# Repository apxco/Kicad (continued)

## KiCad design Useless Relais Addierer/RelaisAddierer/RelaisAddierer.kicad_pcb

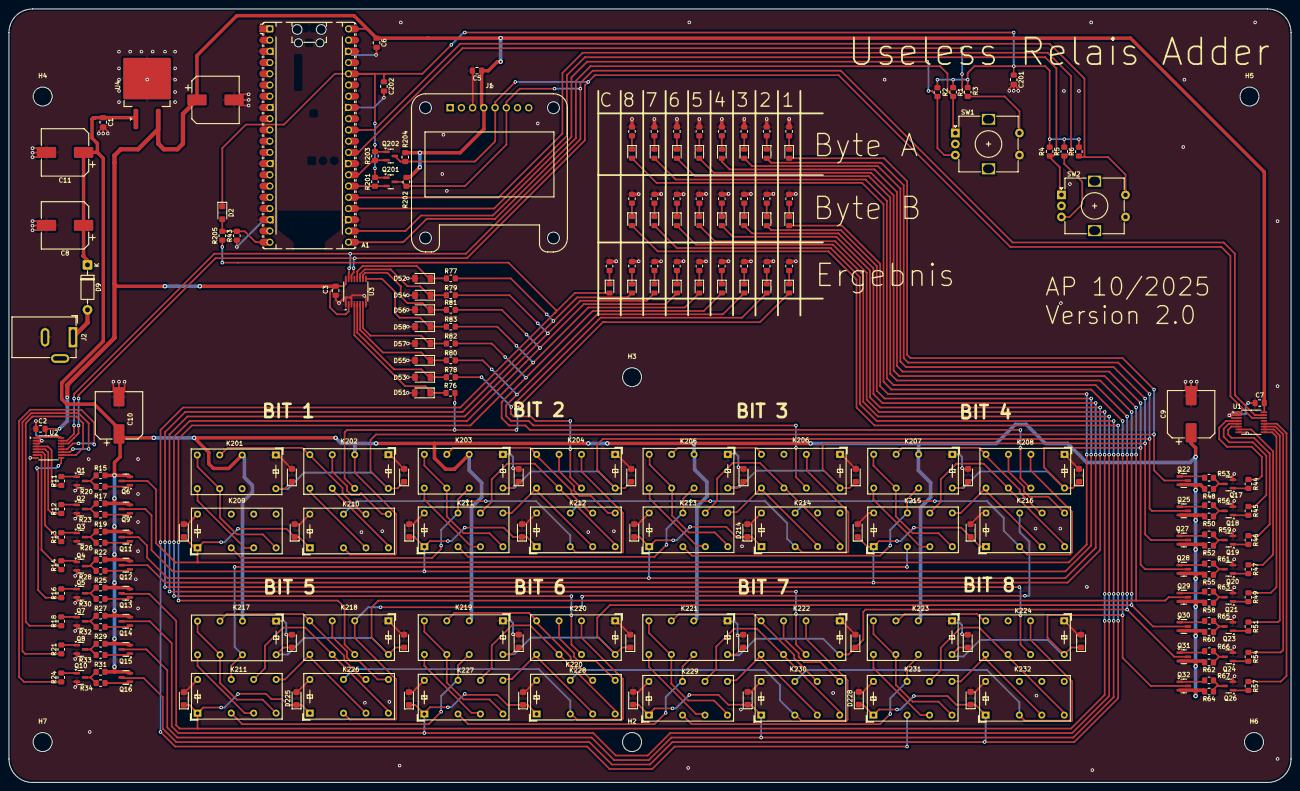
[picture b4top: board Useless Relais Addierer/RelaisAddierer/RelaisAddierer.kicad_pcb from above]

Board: 2 copper layers, 290.1 x 175.0 mm, 254 parts (0 on the bottom side), 198 nets.

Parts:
A1: RaspberryPi_Pico; RaspberryPi_Pico_Common_Unspecified
C1: 1uF; C_0805_2012Metric_Pad1.18x1.45mm_HandSolder
C2, C3, C5, C6, C7, C201, C202: 100nF; C_0805_2012Metric_Pad1.18x1.45mm_HandSolder
C8, C9, C10, C11, C12: 470uF; CP_Elec_10x12.5
D2, D201, D202, D203, D204, D205, D206, D207, D208, D209, D210, D211, D212, D213, D214, D215, D216, D217, D218, D219, D220, D221, D222, D223, D224, D225, D226, D227, D228, D229, D230, D231, D232: 1N4148WT; D_SMF
D9: 1N4007; D_DO-41_SOD81_P10.16mm_Horizontal
D34, D35, D36, D37, D38, D39, D40, D41, D43, D44, D45, D46, D47, D48, D49, D50, D59, D60, D61, D62, D63, D64, D65, D66, D67: LED; LED_0805_2012Metric_Pad1.15x1.40mm_HandSolder
D51, D52, D53, D54, D55, D56, D57, D58: BZD27C47; D_MiniMELF
H2, H3, H4, H5, H6, H7: MountingHole; MountingHole_4.3mm_M4_DIN965
J1: Conn_01x08_Pin; Adafruit_SSD1306
J2: Barrel_Jack; BarrelJack_GCT_DCJ200-10-A_Horizontal
K201, K202, K203, K204, K205, K206, K207, K208, K209, K210, K211, K212, K213, K214, K215, K216, K217, K218, K219, K220, K221, K222, K223, K224, K225, K226, K227, K228, K229, K230, K231, K232: HK19F-DCxxV-SHC; Relay_DPDT_Finder_30.22
Q1, Q2, Q3, Q4, Q5, Q7, Q8, Q10, Q17, Q18, Q19, Q20, Q21, Q23, Q24, Q26: BC847; SOT-23
Q6: PJM10H01PSA; SOT-23
Q9, Q11, Q12, Q13, Q14, Q15, Q16, Q22, Q25, Q27, Q28, Q29, Q30, Q31, Q32: DMP3099L; SOT-23
Q201, Q202: BSS138; SOT-23
R1, R2, R3, R4, R5, R6, R15, R17, R19, R22, R25, R27, R29, R31, R48, R50, R52, R55, R58, R60, R62, R64, R201, R202, R203, R204: 10k; R_0805_2012Metric_Pad1.20x1.40mm_HandSolder
R11, R12, R13, R14, R16, R18, R20, R21, R23, R24, R26, R28, R30, R32, R33, R34, R44, R45, R46, R47, R49, R51, R53, R54, R56, R57, R59, R61, R63, R65, R66, R67: 100R; R_0805_2012Metric_Pad1.20x1.40mm_HandSolder
R35, R36, R37, R38, R39, R40, R41, R42, R43, R68, R69, R70, R71, R72, R73, R74, R75, R84, R85, R86, R87, R88, R89, R90, R91, R92: 1k; R_0805_2012Metric_Pad1.20x1.40mm_HandSolder
R76, R77, R78, R79, R80, R81, R82, R83: 560; R_0805_2012Metric_Pad1.20x1.40mm_HandSolder
R205: 2,6k; R_0805_2012Metric_Pad1.20x1.40mm_HandSolder
SW1, SW2: RotaryEncoder_Switch; RotaryEncoder_Alps_EC12E-Switch_Vertical_H20mm
U1, U2, U3: TCA9534; TSSOP-16_4.4x5mm_P0.65mm
U4: uA7805; TO-263-2

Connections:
+3.3V: A1.36 (3V3), C201.1, C202.1, D2.1 (K), Q201.1 (G), Q202.1 (G), R1.1, R2.2, R3.2, R4.1, R5.2, R6.2, R201.2, R203.2
+5V: A1.40 (VBUS), C2.1, C3.1, C5.1, C6.1, C7.1, C12.1, J1.4, R202.2, R204.2, U1.16 (VDD), U2.1 (A0), U2.16 (VDD), U3.2 (A1), U3.16 (VDD), U4.3 (OUT)
+12V: C1.1, C8.1, C9.1, C10.1, C11.1, D9.1 (K), K201.11, K202.11, K203.11, K205.11, K207.11, K210.11, K217.11, K219.11, K221.11, K223.11, Q6.2 (S), Q9.2 (S), Q11.2 (S), Q12.2 (S), Q13.2 (S), Q14.2 (S), Q15.2 (S), Q16.2 (S), Q22.2 (S), Q25.2 (S), Q27.2 (S), Q28.2 (S), Q29.2 (S), Q30.2 (S), Q31.2 (S), Q32.2 (S), R15.2, R17.2, R19.2, R22.2, R25.2, R27.2, R29.2, R31.2, R48.2, R50.2, R52.2, R55.2, R58.2, R60.2, R62.2, R64.2, U4.1 (IN)
Bit A.1: D43.2 (A), D201.1 (K), D204.1 (K), K201.A2, K202.A2, Q22.3 (D)
Bit A.2: D44.2 (A), D205.1 (K), D208.1 (K), K203.A2, K204.A2, Q25.3 (D)
Bit A.3: D45.2 (A), D202.1 (K), D206.1 (K), K205.A2, K206.A2, Q27.3 (D)
Bit A.4: D46.2 (A), D203.1 (K), D207.1 (K), K207.A2, K208.A2, Q28.3 (D)
Bit A.5: D47.2 (A), D217.1 (K), D221.1 (K), K217.A2, K218.A2, Q29.3 (D)
Bit A.6: D48.2 (A), D220.1 (K), D224.1 (K), K219.A2, K220.A2, Q30.3 (D)
Bit A.7: D49.2 (A), D218.1 (K), D222.1 (K), K221.A2, K222.A2, Q31.3 (D)
Bit A.8: D50.2 (A), D219.1 (K), D223.1 (K), K223.A2, K224.A2, Q32.3 (D)
Bit B.1: D34.2 (A), D209.1 (K), D210.1 (K), K209.A1, K210.A1, Q6.3 (D)
Bit B.2: D35.2 (A), D213.1 (K), D216.1 (K), K211.A1, K212.A1, Q9.3 (D)
Bit B.3: D36.2 (A), D211.1 (K), D214.1 (K), K213.A1, K214.A1, Q11.3 (D)
Bit B.4: D37.2 (A), D212.1 (K), D215.1 (K), K215.A1, K216.A1, Q12.3 (D)
Bit B.5: D38.2 (A), D225.1 (K), D226.1 (K), K225.A1, K226.A1, Q13.3 (D)
Bit B.6: D39.2 (A), D229.1 (K), D232.1 (K), K227.A1, K228.A1, Q14.3 (D)
Bit B.7: D40.2 (A), D227.1 (K), D230.1 (K), K229.A1, K230.A1, Q15.3 (D)
Bit B.8: D41.2 (A), D228.1 (K), D231.1 (K), K231.A1, K232.A1, Q16.3 (D)
CLK1: A1.21 (GPIO16), R1.2, SW1.A
CLK2: A1.24 (GPIO18), R4.2, SW2.A
Carry_Bit1: K203.21, K209.11, K211.21
Carry_Bit1_neg: K204.11, K210.21, K212.11
Carry_Bit2: K205.21, K211.11, K213.21
Carry_Bit2_neg: K206.11, K212.21, K214.11
Carry_Bit3: K207.21, K213.11, K215.21
Carry_Bit3_neg: K208.11, K214.21, K216.11
Carry_Bit4: K215.11, K217.21, K225.21
Carry_Bit4_neg: K216.21, K218.11, K226.11
Carry_Bit5: K219.21, K225.11, K227.21
Carry_Bit5_neg: K220.11, K226.21, K228.11
Carry_Bit6: K221.21, K227.11, K229.21
Carry_Bit6_neg: K222.11, K228.21, K230.11
Carry_Bit7: K223.21, K229.11, K231.21
Carry_Bit7_neg: K224.11, K230.21, K232.11
Carry_Bit8: D59.2 (A), K231.11, R205.1
DT1: A1.22 (GPIO17), R2.1, SW1.B
DT2: A1.25 (GPIO19), R5.1, SW2.B
GND: A1.3 (GND), A1.8 (GND), A1.13 (GND), A1.18 (GND), A1.23 (GND), A1.28 (GND), A1.33 (AGND), A1.38 (GND), C1.2, C2.2, C3.2, C5.2, C6.2, C7.2, C8.2, C9.2, C10.2, C11.2, C12.2, C201.2, C202.2, D51.2 (A), D52.2 (A), D53.2 (A), D54.2 (A), D55.2 (A), D56.2 (A), D57.2 (A), D58.2 (A), D201.2 (A), D202.2 (A), D203.2 (A), D204.2 (A), D205.2 (A), D206.2 (A), D207.2 (A), D208.2 (A), D209.2 (A), D210.2 (A), D211.2 (A), D212.2 (A), D213.2 (A), D214.2 (A), D215.2 (A), D216.2 (A), D217.2 (A), D218.2 (A), D219.2 (A), D220.2 (A), D221.2 (A), D222.2 (A), D223.2 (A), D224.2 (A), D225.2 (A), D226.2 (A), D227.2 (A), D228.2 (A), D229.2 (A), D230.2 (A), D231.2 (A), D232.2 (A), J1.3, J2.2, K201.A1, K202.A1, K203.A1, K204.A1, K205.A1, K206.A1, K207.A1, K208.A1, K209.A2, K210.A2, K211.A2, K212.A2, K213.A2, K214.A2, K215.A2, K216.A2, K217.A1, K218.A1, K219.A1, K220.A1, K221.A1, K222.A1, K223.A1, K224.A1, K225.A2, K226.A2, K227.A2, K228.A2, K229.A2, K230.A2, K231.A2, K232.A2, Q1.2 (E), Q2.2 (E), Q3.2 (E), Q4.2 (E), Q5.2 (E), Q7.2 (E), Q8.2 (E), Q10.2 (E), Q17.2 (E), Q18.2 (E), Q19.2 (E), Q20.2 (E), Q21.2 (E), Q23.2 (E), Q24.2 (E), Q26.2 (E), R35.2, R36.2, R37.2, R38.2, R39.2, R40.2, R41.2, R42.2, R43.1, R68.2, R69.2, R70.2, R71.2, R72.2, R73.2, R74.2, R75.2, R84.2, R85.2, R86.2, R87.2, R88.2, R89.2, R90.2, R91.2, R92.2, SW1.C, SW1.S2, SW2.C, SW2.S2, U1.1 (A0), U1.2 (A1), U1.3 (A2), U1.8 (GND), U2.2 (A1), U2.3 (A2), U2.8 (GND), U3.1 (A0), U3.3 (A2), U3.8 (GND), U4.2 (GND)
I2C0 SCL: J1.5, Q202.3 (D), R204.1, U1.14 (SCL), U2.14 (SCL), U3.14 (SCL)
I2C0 SDA: J1.6, Q201.3 (D), R202.1, U1.15 (SDA), U2.15 (SDA), U3.15 (SDA)
unnamed: A1.20 (GPIO15), D2.2 (A), R43.2, R205.2
unnamed: A1.26 (GPIO20), Q201.2 (S), R201.1
unnamed: A1.27 (GPIO21), Q202.2 (S), R203.1
unnamed: D9.2 (A), J2.1
unnamed: D34.1 (K), R35.1
unnamed: D35.1 (K), R36.1
unnamed: D36.1 (K), R37.1
unnamed: D37.1 (K), R38.1
unnamed: D38.1 (K), R39.1
unnamed: D39.1 (K), R40.1
unnamed: D40.1 (K), R41.1
unnamed: D41.1 (K), R42.1
unnamed: D43.1 (K), R68.1
unnamed: D44.1 (K), R69.1
unnamed: D45.1 (K), R70.1
unnamed: D46.1 (K), R71.1
unnamed: D47.1 (K), R72.1
unnamed: D48.1 (K), R73.1
unnamed: D49.1 (K), R74.1
unnamed: D50.1 (K), R75.1
unnamed: D51.1 (K), R76.1, U3.4 (P0)
unnamed: D52.1 (K), R77.1, U3.12 (P7)
unnamed: D53.1 (K), R78.1, U3.5 (P1)
unnamed: D54.1 (K), R79.1, U3.11 (P6)
unnamed: D55.1 (K), R80.1, U3.6 (P2)
unnamed: D56.1 (K), R81.1, U3.10 (P5)
unnamed: D57.1 (K), R82.1, U3.7 (P3)
unnamed: D58.1 (K), R83.1, U3.9 (P4)
unnamed: D59.1 (K), R84.1
unnamed: D60.1 (K), R85.1
unnamed: D61.1 (K), R86.1
unnamed: D62.1 (K), R87.1
unnamed: D63.1 (K), R88.1
unnamed: D64.1 (K), R89.1
unnamed: D65.1 (K), R90.1
unnamed: D66.1 (K), R91.1
unnamed: D67.1 (K), R92.1
unnamed: K201.12, K202.14, K210.22
unnamed: K201.14, K201.22, K209.14
unnamed: K201.24, K209.12
unnamed: K202.12, K210.24
unnamed: K202.22, K210.14
unnamed: K202.24, K210.12
unnamed: K203.12, K204.14, K212.22
unnamed: K203.14, K203.22, K211.14
unnamed: K203.24, K211.12
unnamed: K204.12, K212.24
unnamed: K204.22, K211.22, K212.14
unnamed: K204.24, K211.24, K212.12
unnamed: K205.12, K206.14
unnamed: K205.14, K205.22, K213.14
unnamed: K205.24, K213.12
unnamed: K206.22, K213.22, K214.14
unnamed: K206.24, K213.24, K214.12
unnamed: K207.12, K208.14, K216.22
unnamed: K207.14, K207.22, K215.14
unnamed: K207.24, K215.12
unnamed: K208.12, K216.24
unnamed: K208.22, K215.22, K216.14
unnamed: K208.24, K215.24, K216.12
unnamed: K217.12, K218.14, K226.22
unnamed: K217.14, K217.22, K225.14
unnamed: K217.24, K225.12
unnamed: K218.12, K226.24
unnamed: K218.22, K225.22, K226.14
unnamed: K218.24, K225.24, K226.12
unnamed: K219.12, K220.14, K228.22
unnamed: K219.14, K219.22, K227.14
unnamed: K219.24, K227.12
unnamed: K220.12, K228.24
unnamed: K220.22, K227.22, K228.14
unnamed: K220.24, K227.24, K228.12
unnamed: K221.12, K222.14, K230.22
unnamed: K221.14, K221.22, K229.14
unnamed: K221.24, K229.12
unnamed: K222.12, K230.24
unnamed: K222.22, K229.22, K230.14
unnamed: K222.24, K229.24, K230.12
unnamed: K223.12, K224.14
unnamed: K223.14, K223.22, K231.14
unnamed: K223.24, K231.12
unnamed: K224.22, K231.22, K232.14
unnamed: K224.24, K231.24, K232.12
unnamed: Q1.1 (B), R11.2
unnamed: Q1.3 (C), R15.1, R20.1
unnamed: Q2.1 (B), R12.2
unnamed: Q2.3 (C), R17.1, R23.1
unnamed: Q3.1 (B), R13.2
unnamed: Q3.3 (C), R19.1, R26.1
unnamed: Q4.1 (B), R14.2
unnamed: Q4.3 (C), R22.1, R28.1
unnamed: Q5.1 (B), R16.2
unnamed: Q5.3 (C), R25.1, R30.1
unnamed: Q6.1 (G), R20.2
unnamed: Q7.1 (B), R18.2
unnamed: Q7.3 (C), R27.1, R32.1
unnamed: Q8.1 (B), R21.2
unnamed: Q8.3 (C), R29.1, R33.1
unnamed: Q9.1 (G), R23.2
unnamed: Q10.1 (B), R24.2
unnamed: Q10.3 (C), R31.1, R34.1
unnamed: Q11.1 (G), R26.2
unnamed: Q12.1 (G), R28.2
unnamed: Q13.1 (G), R30.2
unnamed: Q14.1 (G), R32.2
unnamed: Q15.1 (G), R33.2
unnamed: Q16.1 (G), R34.2
unnamed: Q17.1 (B), R44.2
unnamed: Q17.3 (C), R48.1, R53.1
unnamed: Q18.1 (B), R45.2
unnamed: Q18.3 (C), R50.1, R56.1
unnamed: Q19.1 (B), R46.2
unnamed: Q19.3 (C), R52.1, R59.1
unnamed: Q20.1 (B), R47.2
unnamed: Q20.3 (C), R55.1, R61.1
unnamed: Q21.1 (B), R49.2
unnamed: Q21.3 (C), R58.1, R63.1
unnamed: Q22.1 (G), R53.2
unnamed: Q23.1 (B), R51.2
unnamed: Q23.3 (C), R60.1, R65.1
unnamed: Q24.1 (B), R54.2
unnamed: Q24.3 (C), R62.1, R66.1
unnamed: Q25.1 (G), R56.2
unnamed: Q26.1 (B), R57.2
unnamed: Q26.3 (C), R64.1, R67.1
unnamed: Q27.1 (G), R59.2
unnamed: Q28.1 (G), R61.2
unnamed: Q29.1 (G), R63.2
unnamed: Q30.1 (G), R65.2
unnamed: Q31.1 (G), R66.2
unnamed: Q32.1 (G), R67.2
unnamed: R44.1, U1.4 (P0)
unnamed: R45.1, U1.5 (P1)
unnamed: R46.1, U1.6 (P2)
unnamed: R47.1, U1.7 (P3)
unnamed: R49.1, U1.9 (P4)
unnamed: R51.1, U1.10 (P5)
unnamed: R54.1, U1.11 (P6)
unnamed: R57.1, U1.12 (P7)
unnamed: R11.1, U2.4 (P0)
unnamed: R12.1, U2.5 (P1)
unnamed: R13.1, U2.6 (P2)
unnamed: R14.1, U2.7 (P3)
unnamed: R16.1, U2.9 (P4)
unnamed: R18.1, U2.10 (P5)
unnamed: R21.1, U2.11 (P6)
unnamed: R24.1, U2.12 (P7)
SW1: A1.29 (GPIO22), R3.1, SW1.S1
SW2: A1.31 (GPIO26_ADC0), R6.1, SW2.S1
Summ_Bit1: D67.2 (A), K202.21, R76.2
Summ_Bit2: D66.2 (A), K204.21, R78.2
Summ_Bit3: D65.2 (A), K206.21, R80.2
Summ_Bit4: D64.2 (A), K208.21, R82.2
Summ_Bit5: D63.2 (A), K218.21, R83.2
Summ_Bit6: D62.2 (A), K220.21, R81.2
Summ_Bit7: D61.2 (A), K222.21, R79.2
Summ_Bit8: D60.2 (A), K224.21, R77.2

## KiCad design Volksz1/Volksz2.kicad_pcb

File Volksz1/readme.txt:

Hat für RaspberryPi, Spannungsversorung und Interface für Volkszähler.

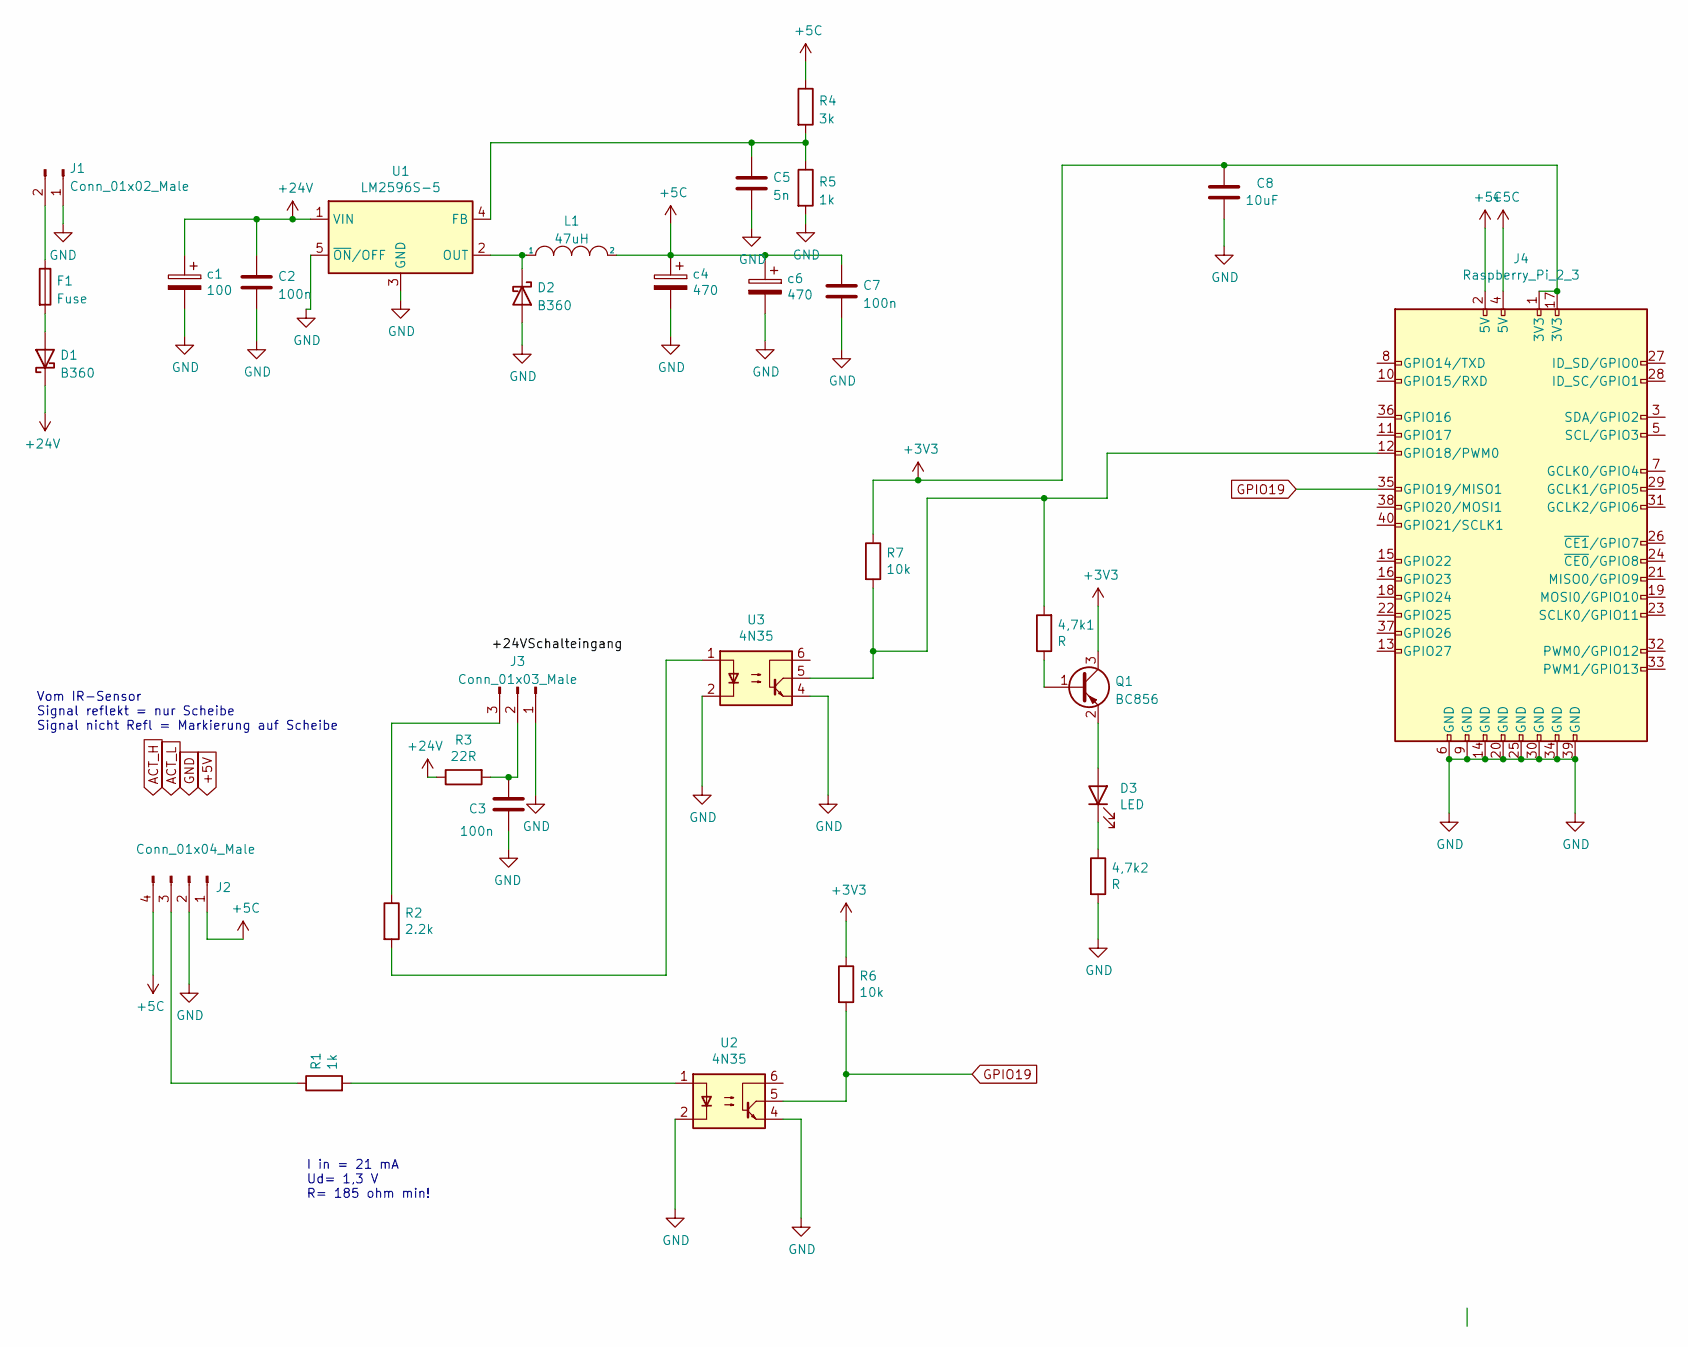
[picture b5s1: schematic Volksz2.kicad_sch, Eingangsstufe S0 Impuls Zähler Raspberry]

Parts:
4,7k1, 4,7k2: R; R_0805_2012Metric_Pad1.20x1.40mm_HandSolder
C2, C3, C7: 100n; C_0805_2012Metric_Pad1.18x1.45mm_HandSolder
C5: 5n; C_0805_2012Metric_Pad1.18x1.45mm_HandSolder
C8: 10uF; R_0805_2012Metric_Pad1.20x1.40mm_HandSolder
D1, D2: B360; D_SMC
D3: LED; D_0805_2012Metric_Pad1.15x1.40mm_HandSolder
F1: Fuse; Fuse_0805_2012Metric_Pad1.15x1.40mm_HandSolder
J1: Conn_01x02_Male; PinSocket_1x02_P2.54mm_Vertical
J2: Conn_01x04_Male; PinHeader_1x04_P2.54mm_Vertical
J3: Conn_01x03_Male; PinHeader_1x03_P2.54mm_Vertical
J4: Raspberry_Pi_2_3; PinSocket_2x20_P2.54mm_Vertical
L1: 47uH; L_Wuerth_HCI-1040
Q1: BC856; SOT-23
R1, R5: 1k; R_0805_2012Metric_Pad1.20x1.40mm_HandSolder
R2: 2.2k; R_0805_2012Metric_Pad1.20x1.40mm_HandSolder
R3: 22R; R_1206_3216Metric_Pad1.30x1.75mm_HandSolder
R4: 3k; R_0805_2012Metric_Pad1.20x1.40mm_HandSolder
R6, R7: 10k; R_0805_2012Metric_Pad1.20x1.40mm_HandSolder
U1: LM2596S-5; TO-263-5_TabPin3
U2, U3: 4N35; DIP-6_W7.62mm
c1: 100; CP_Elec_10x12.6
c4, c6: 470; CP_Elec_10x12.6

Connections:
+3V3: C8.1, J4.1 (3V3), J4.17 (3V3), Q1.3 (C), R6.1, R7.1
+5C: C7.1, J2.1, J2.4, J4.2 (5V), J4.4 (5V), L1.2, R4.1, c4.1, c6.1
+24V: C2.1, D1.1 (K), R3.1, U1.1 (VIN), c1.1
GND: 4,7k2.2, C2.2, C3.2, C5.2, C7.2, C8.2, D2.2 (A), J1.1, J2.2, J3.1, J4.6 (GND), J4.9 (GND), J4.14 (GND), J4.20 (GND), J4.25 (GND), J4.30 (GND), J4.34 (GND), J4.39 (GND), R5.2, U1.3 (GND), U1.5 (~ON/OFF), U2.2, U2.4, U3.2, U3.4, c1.2, c4.2, c6.2
GPIO19: J4.35 (GPIO19/MISO1), R6.2, U2.5
unnamed: 4,7k1.1, Q1.1 (B)
unnamed: 4,7k1.2, J4.12 (GPIO18/PWM0), R7.2, U3.5
unnamed: 4,7k2.1, D3.1 (K)
unnamed: C3.1, J3.2, R3.2
unnamed: C5.1, R4.2, R5.1, U1.4 (FB)
unnamed: D1.2 (A), F1.2
unnamed: D2.1 (K), L1.1, U1.2 (OUT)
unnamed: D3.2 (A), Q1.2 (E)
unnamed: F1.1, J1.2
unnamed: J2.3, R1.1
unnamed: J3.3, R2.1
unnamed: R1.2, U2.1
unnamed: R2.2, U3.1

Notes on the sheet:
Vom IR-Sensor Signal reflekt = nur Scheibe Signal nicht Refl = Markierung auf Scheibe
I in = 21 mA Ud= 1,3 V R= 185 ohm min!

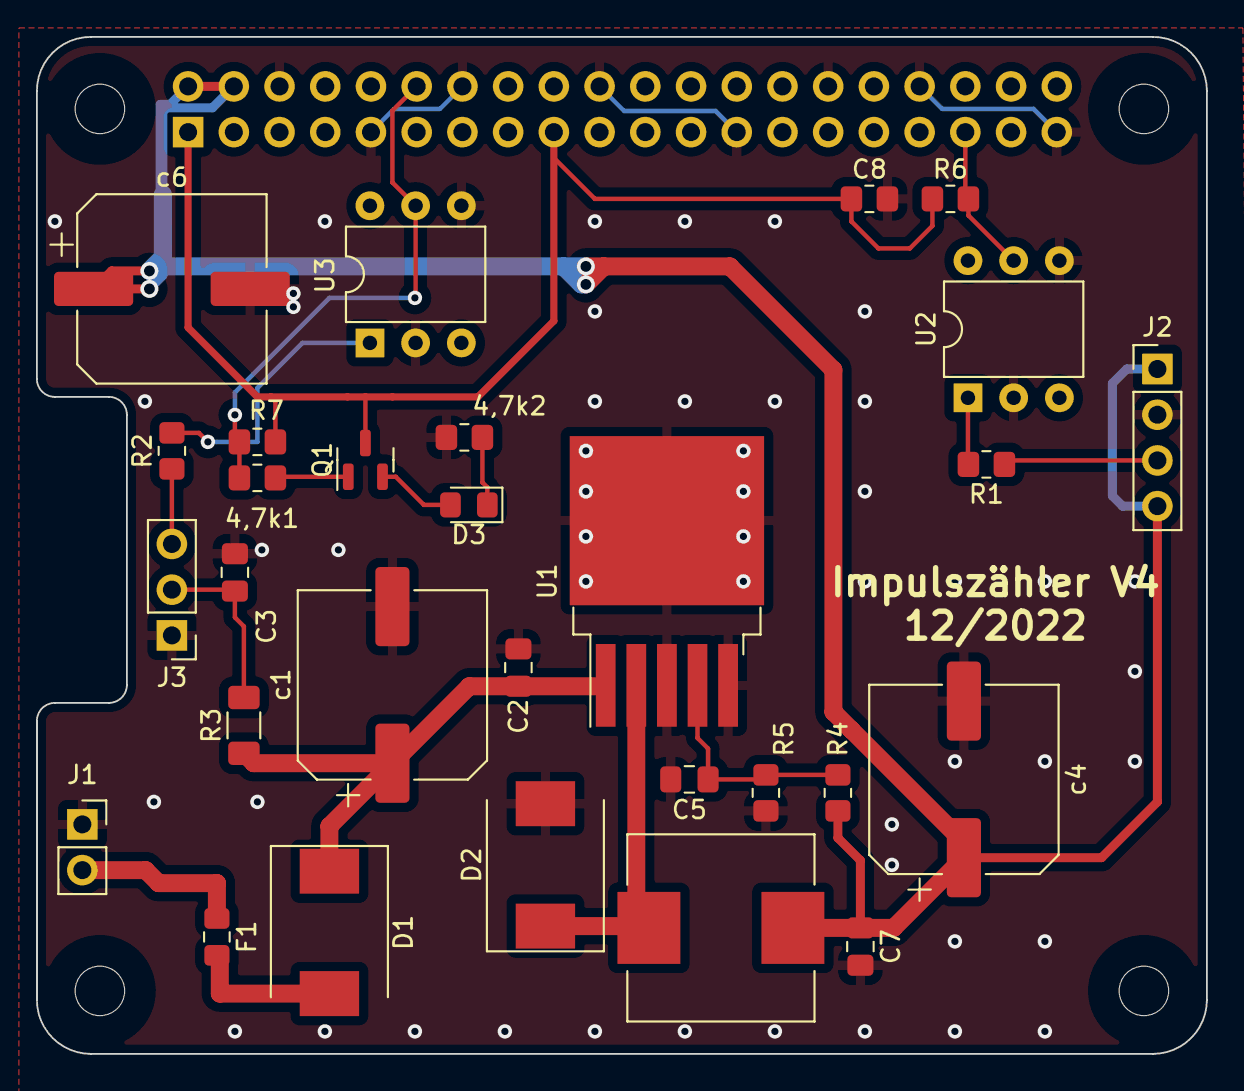
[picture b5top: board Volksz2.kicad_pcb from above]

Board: 2 copper layers, 65.0 x 56.5 mm, 30 parts (1 on the bottom side), 18 nets.

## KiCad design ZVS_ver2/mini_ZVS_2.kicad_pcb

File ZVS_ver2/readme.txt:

Klassischer Aufbau eines Royer-Oszillator

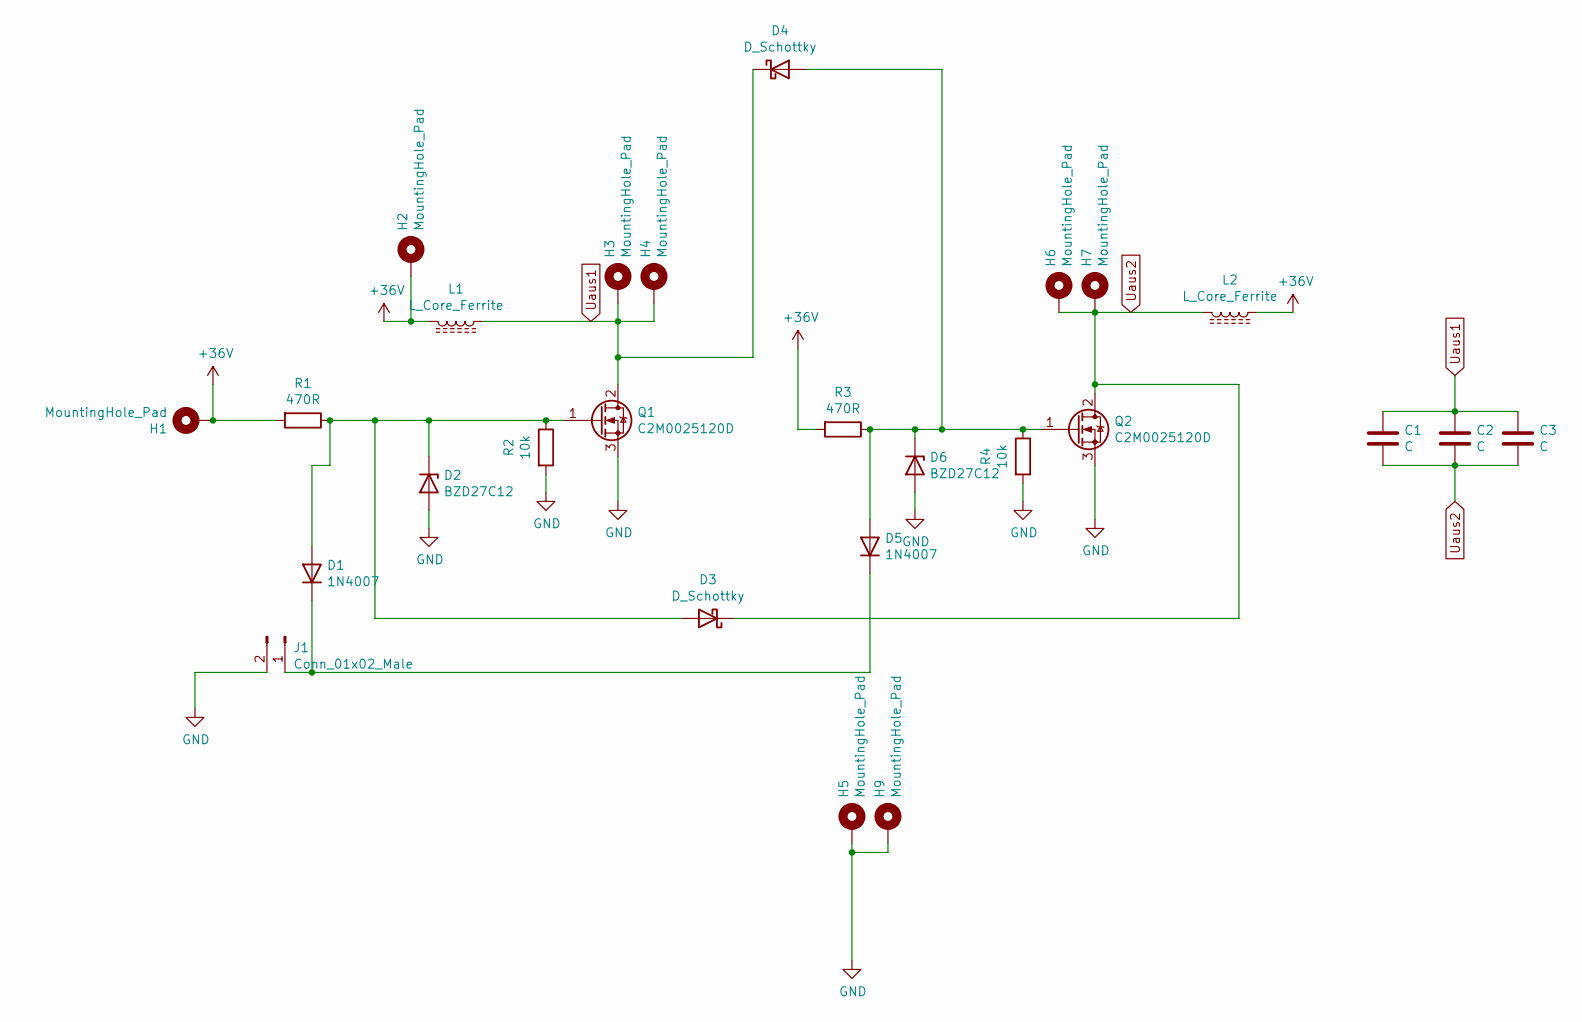
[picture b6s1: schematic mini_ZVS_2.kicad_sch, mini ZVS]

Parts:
C1, C2, C3: C; C_Rect_L24.0mm_W10.1mm_P22.50mm_MKT
D1, D5: 1N4007; D_DO-41_SOD81_P10.16mm_Horizontal
D2, D6: BZD27C12; D_DO-41_SOD81_P10.16mm_Horizontal
D3, D4: D_Schottky; D_DO-41_SOD81_P10.16mm_Horizontal
H1, H2, H4, H6: MountingHole_Pad; MountingHole_2.2mm_M2_Pad_Via
H3, H5, H7, H9: MountingHole_Pad; MountingHole_3.2mm_M3_DIN965_Pad
J1: Conn_01x02_Male; PinHeader_1x02_P2.54mm_Vertical
L1, L2: L_Core_Ferrite; L_Toroid_Vertical_L17.8mm_W9.7mm_P7.11mm_Pulse_B
Q1, Q2: C2M0025120D; TO-247-3_Vertical
R1, R3: 470R; R_Axial_Power_L20.0mm_W6.4mm_P7.62mm_Vertical
R2, R4: 10k; R_Axial_DIN0204_L3.6mm_D1.6mm_P7.62mm_Horizontal

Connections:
+36V: H1.1, H2.1, L1.2, L2.1, R1.2, R3.2
GND: D2.2 (A), D6.2 (A), H5.1, H9.1, J1.2, Q1.3 (S), Q2.3 (S), R2.2, R4.2
unnamed: D1.1 (K), D5.1 (K), J1.1
unnamed: D1.2 (A), D2.1 (K), D3.2 (A), Q1.1 (G), R1.1, R2.1
unnamed: D4.2 (A), D5.2 (A), D6.1 (K), Q2.1 (G), R3.1, R4.1
Uaus1: C1.1, C2.1, C3.1, D4.1 (K), H3.1, H4.1, L1.1, Q1.2 (D)
Uaus2: C1.2, C2.2, C3.2, D3.1 (K), H6.1, H7.1, L2.2, Q2.2 (D)

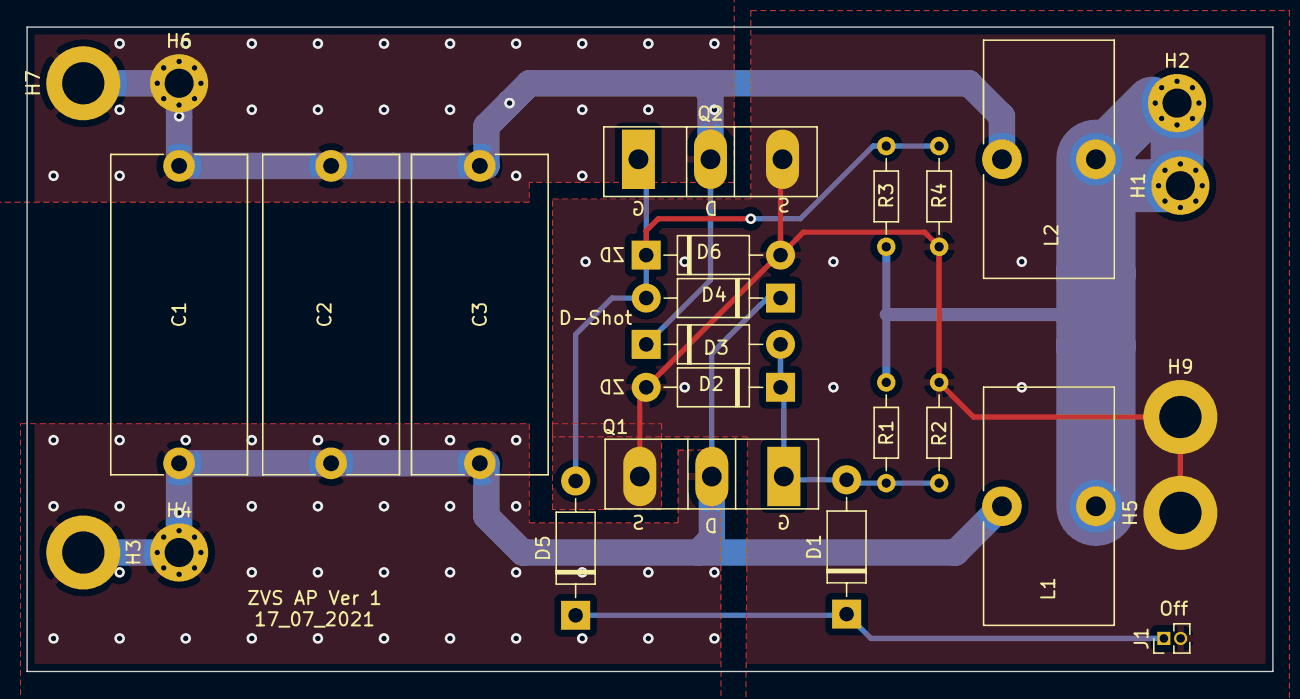
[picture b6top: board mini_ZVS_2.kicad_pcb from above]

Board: 2 copper layers, 94.2 x 48.8 mm, 26 parts (0 on the bottom side), 7 nets.

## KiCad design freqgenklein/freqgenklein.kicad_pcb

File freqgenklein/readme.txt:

Kleiner Oszillator zu testzwecken

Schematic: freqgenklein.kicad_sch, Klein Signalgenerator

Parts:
C1, C4, C6: 100nF; C_0805_2012Metric_Pad1.18x1.45mm_HandSolder
C2, C7: 100n; C_Axial_L3.8mm_D2.6mm_P7.50mm_Horizontal
C3: 100n; C_0805_2012Metric_Pad1.18x1.45mm_HandSolder
C5: 100uF; CP_Elec_10x10.5
D1, D2: D; D_0805_2012Metric_Pad1.15x1.40mm_HandSolder
D3, D4: D; C_0805_2012Metric_Pad1.18x1.45mm_HandSolder
D5: LED; LED_0805_2012Metric_Pad1.15x1.40mm_HandSolder
Duty1: 1k; Potentiometer_Bourns_3296W_Vertical
Freq.1: 10k; Potentiometer_Bourns_3296W_Vertical
H1, H2: MountingHole_Pad; MountingHole_3.2mm_M3_DIN965_Pad
J1, J2, J3, J4: Conn_01x06; PinSocket_1x06_P2.54mm_Vertical
JP1: SolderJumper_2_Open; SolderJumper-2_P1.3mm_Open_TrianglePad1.0x1.5mm
R1, R2, R4, R5: 1k; R_0805_2012Metric_Pad1.20x1.40mm_HandSolder
R3: 10k; R_0805_2012Metric_Pad1.20x1.40mm_HandSolder
U1: 40106; SO-14_3.9x8.65mm_P1.27mm

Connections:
+12V: C1.1, C4.1, C5.1, C6.1, D3.1 (K), J1.6, J2.1, J3.1, J4.1, R3.1, U1.13, U1.14 (VDD)
Ant_in: C7.1, D3.2 (A), D4.1 (K), J1.1
Ant_trg: C2.1, C3.1, Freq.1.2, Freq.1.3, R1.2, R2.2, U1.1
GND: C1.2, C2.2, C3.2, C4.2, C5.2, C6.2, D4.2 (A), D5.2 (A), H1.1, H2.1, J1.2, J1.5, J2.6, J3.6, J4.6, U1.7 (VSS)
unnamed: C7.2, R2.1
unnamed: D1.1 (K), D2.2 (A), Freq.1.1, JP1.1 (A), R1.1
unnamed: D1.2 (A), Duty1.3
unnamed: D2.1 (K), Duty1.1
unnamed: D5.1 (K), R3.2
unnamed: Duty1.2, JP1.2 (B), U1.2, U1.3, U1.5
unnamed: R4.1, U1.4, U1.6, U1.9, U1.11
unnamed: R5.1, U1.8, U1.10
OSC_inv: J1.3, R5.2
Osc: J1.4, R4.2

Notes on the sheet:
HCT7414 R=10k bis 100 C=100nF f=1200Hz -120kHz C=150pF f= 420kHz - 1,7MHz

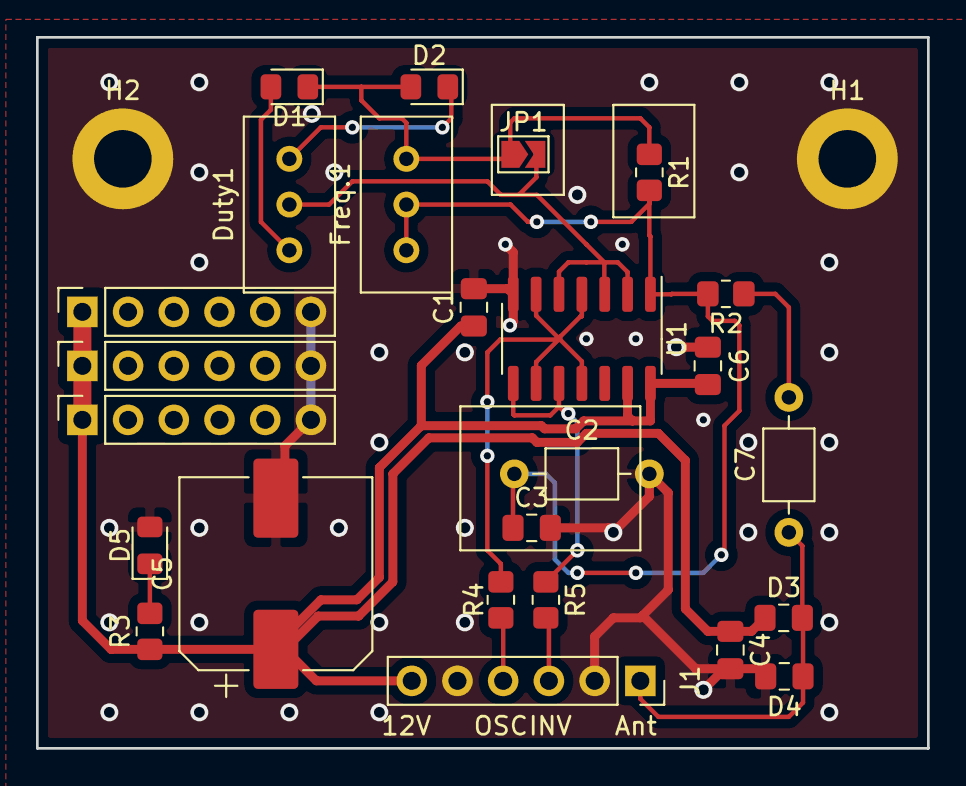
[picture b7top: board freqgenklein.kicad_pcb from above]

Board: 2 copper layers, 49.5 x 39.5 mm, 27 parts (0 on the bottom side), 14 nets.
